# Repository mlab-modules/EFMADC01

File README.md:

# EFMADC01 - Electric Field Mill ADC Module

The **EFMADC01** module is designed to provide an **analog front-end** and **ADC conversion** for [Electric Field Mill sensor](https://github.com/UniversalScientificTechnologies/THUNDERMILL01) development and experiments. It processes analog signals from the field mill electrodes and converts them into digital data for further processing.

## Features

- **High-Precision ADC**: Utilizes the **LTC1865** 16-bit, 250ksps analog-to-digital converter.
- **Low-Noise Analog Front End**: Incorporates **OPA314** operational amplifiers for signal conditioning.
- **Precision and stable Voltage Reference**: Includes a **1.25V reference** for accurate ADC operation.
- **Flexible Power Supply**: Supports **3.3V to 5V** operation.
- **RF Shielding**: Equipped with shielding to reduce external interference.
- **MCX Connector Input**: Enables high-quality signal connection.

## Functional Description

The **EFMADC01** module consists of three main blocks:

1. **Analog Front End (AFE)**:
   - Uses **OPA314** operational amplifiers for signal buffering and amplification.
   - High-impedance resistor (10MΩ) allows direct signal acquisition from the field mill sensor electrodes.

2. **ADC Conversion**:
   - **LTC1865-MS** ADC provides **16-bit resolution** with **250ksps sampling rate**.
   - Accepts differential input signals and supports SPI communication.

3. **Power and Reference**:
   - Powered by an external **3.3V or 5V** supply.
   - Features a **BZV55C-6.2V** Zener diode for overvoltage protection.
   - Uses a **1.25V precision voltage reference** for ADC stability.

## Hardware Connections

### Power Supply:
- **VCC**: Accepts **3.3V to 5V** input.
- **GNDA** and **GND**: Ground connections.

### Analog Input:
- **J9 (MCX Connector)**: Main analog signal input.
- **Operational amplifier stage** conditions the signal before ADC conversion.

## Typical Application

The **EFMADC01** module is primarily used in electric field mill experiments to measure atmospheric electric fields. It can also be employed in low-frequency scientific measurements where high-resolution ADC conversion is required.

## Schematic

For detailed circuit information, please take a look at the [EFMADC01 schematic](/doc/gen/EFMADC01-schematic.pdf) in the documentation.

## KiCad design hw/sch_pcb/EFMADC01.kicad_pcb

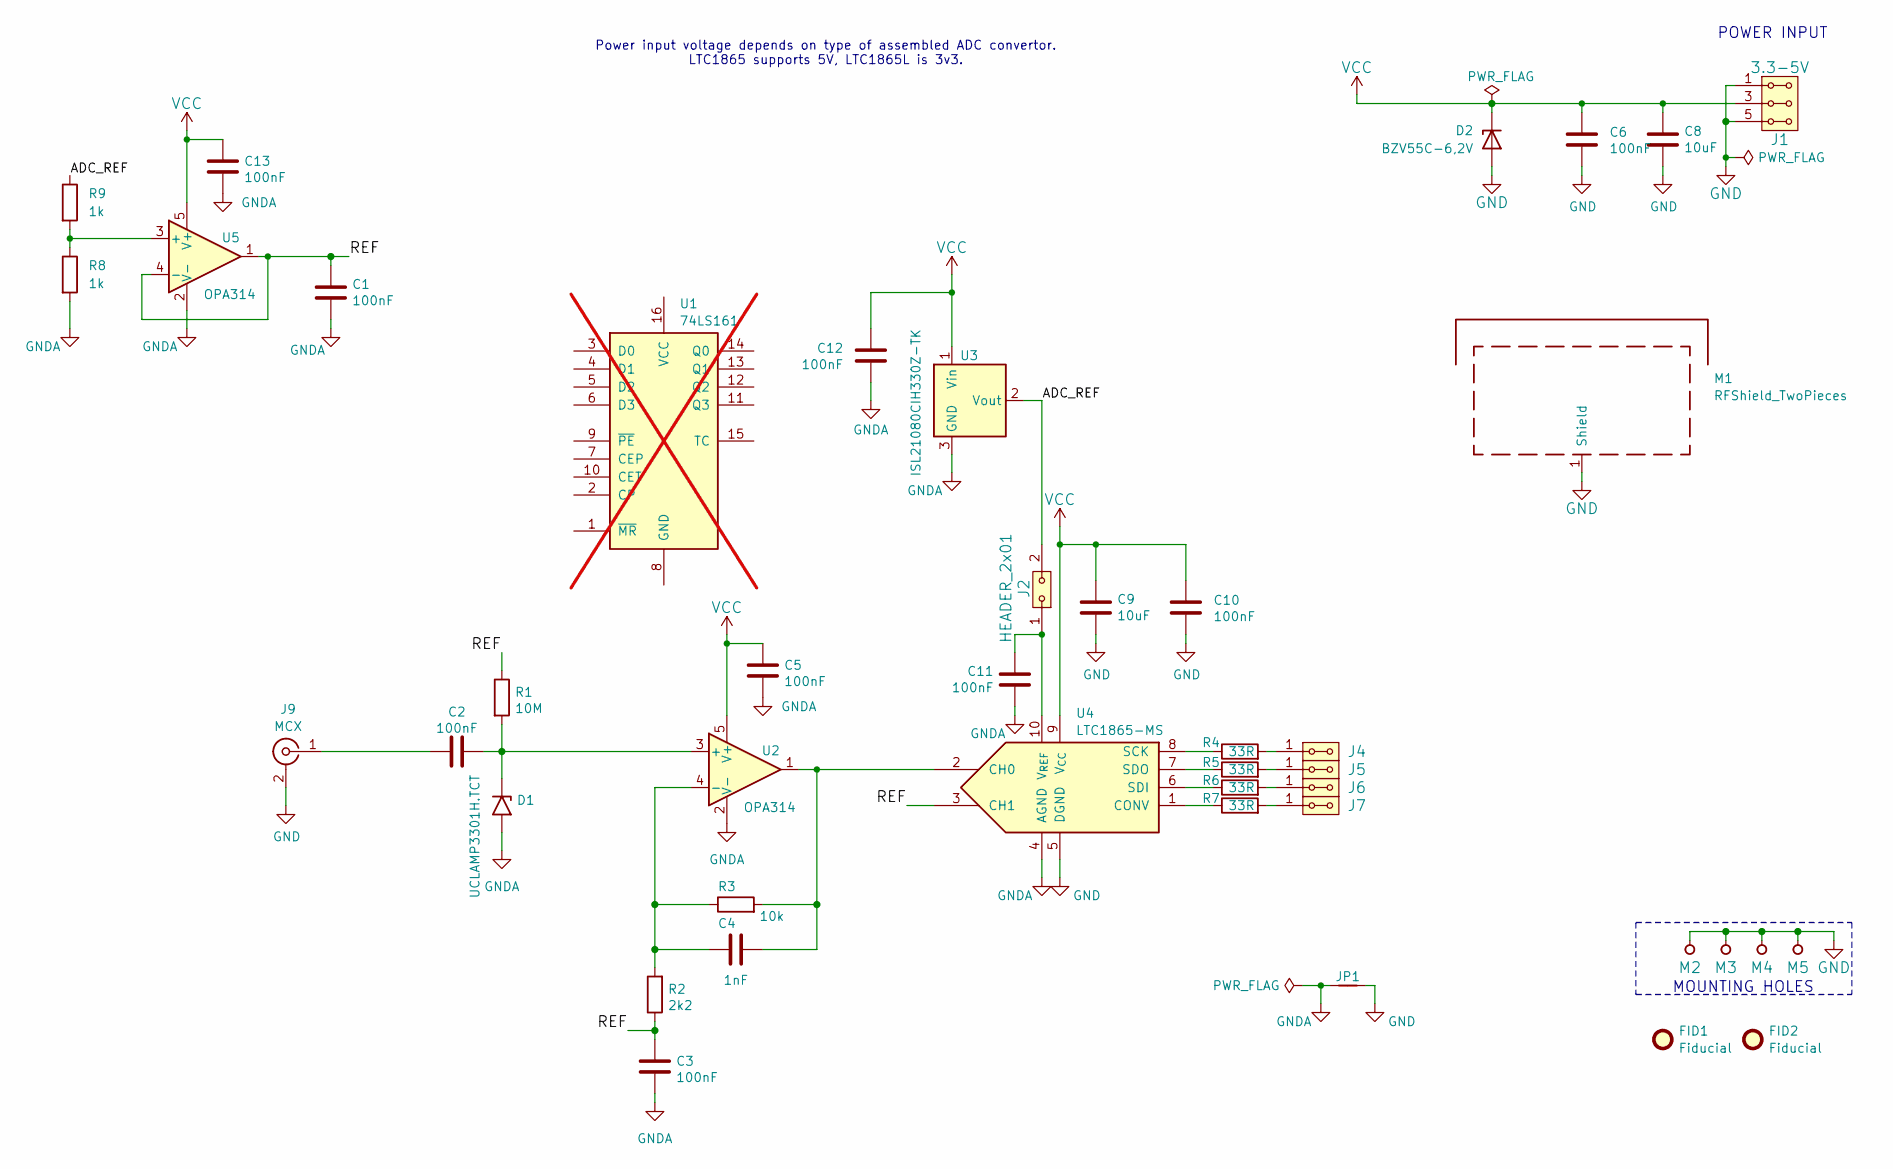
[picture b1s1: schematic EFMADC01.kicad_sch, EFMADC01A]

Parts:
C1, C2, C3, C5, C6, C10, C11, C12, C13: 100nF; C_0805_2012Metric
C4: 1nF; C_0805_2012Metric
C8, C9: 10uF; C_0805_2012Metric
D1: UCLAMP3301H.TCT; D_SMB
D2: BZV55C-6,2V; D_MiniMELF
FID1, FID2: Fiducial; Fiducial_1mm_Mask2mm
J1: 3.3-5V; Straight_2x03
J2: HEADER_2x01; Straight_2x01
J4, J5, J6, J7: HEADER_2x01_PARALLEL; Straight_2x01
J9: MCX; SMA_Amphenol_901-144_Vertical
JP1: Jumper_2_Bridged; NetTie-2_SMD_Pad0.5mm
M1: RFShield_TwoPieces; Laird_Technologies_BMI-S-204-F_32.00x32.00mm
M2, M3, M4, M5: HOLE; MountingHole_3mm
R1: 10M; R_0805_2012Metric
R2: 2k2; R_0805_2012Metric
R3: 10k; R_0805_2012Metric
R4, R5, R6, R7: 33R; R_0805_2012Metric
R8, R9: 1k; R_0805_2012Metric
U1: 74LS161; not fitted
U2, U5: OPA314; SOT-23-5
U3: ISL21080CIH330Z-TK; SOT-23
U4: LTC1865-MS; MSOP-10_3x3mm_P0.5mm

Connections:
/ADC_REF: J2.2, R9.1, U3.2 (Vout)
/REF: C1.1, C3.2, R1.1, R2.1, U4.3 (CH1), U5.1, U5.4 (-)
GND: C6.2, C8.2, C9.2, C10.2, D2.2 (A), J1.1, J1.2, J1.5, J1.6, J9.2 (Ext), JP1.2, M1.1 (Shield), M2.1, M3.1, M4.1, M5.1, U4.5 (DGND)
GNDA: C1.2, C3.1, C5.1, C11.2, C12.2, C13.1, D1.2 (A2), JP1.1, R8.2, U2.2 (V-), U3.3 (GND), U4.4 (AGND), U5.2 (V-)
unnamed: C2.2, D1.1 (A1), R1.2, U2.3 (+)
unnamed: J4.1, J4.2, R4.2
unnamed: J5.1, J5.2, R5.2
unnamed: J6.1, J6.2, R6.2
unnamed: J7.1, J7.2, R7.2
unnamed: C2.1, J9.1 (In)
unnamed: C4.1, R2.2, R3.1, U2.4 (-)
unnamed: C4.2, R3.2, U2.1, U4.2 (CH0)
unnamed: R7.1, U4.1 (CONV)
unnamed: R4.1, U4.8 (SCK)
unnamed: R6.1, U4.6 (SDI)
unnamed: R5.1, U4.7 (SDO)
unnamed: C11.1, J2.1, U4.10 (V_{REF})
unnamed: R8.1, R9.2, U5.3 (+)
VCC: C5.2, C6.1, C8.1, C9.1, C10.1, C12.1, C13.2, D2.1 (K), J1.3, J1.4, U2.5 (V+), U3.1 (Vin), U4.9 (V_{CC}), U5.5 (V+)

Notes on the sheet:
Power input voltage depends on type of assembled ADC convertor. LTC1865 supports 5V, LTC1865L is 3v3.
MOUNTING HOLES
POWER INPUT

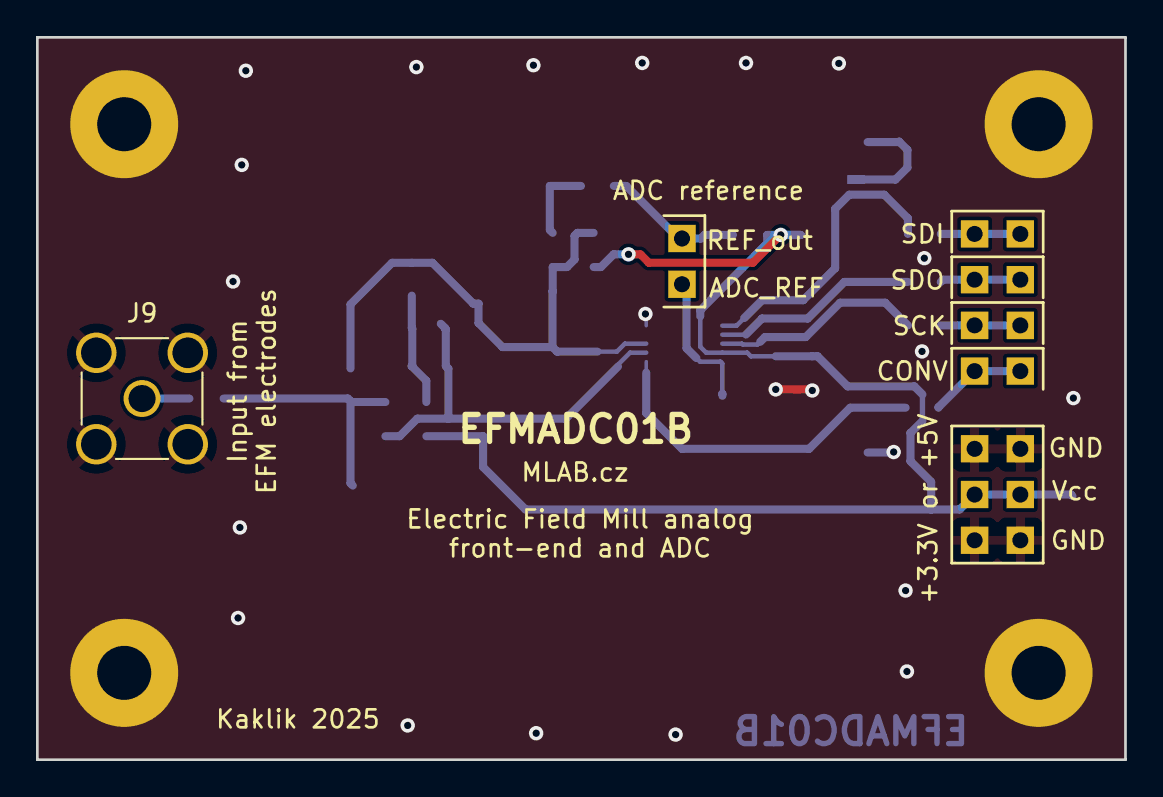
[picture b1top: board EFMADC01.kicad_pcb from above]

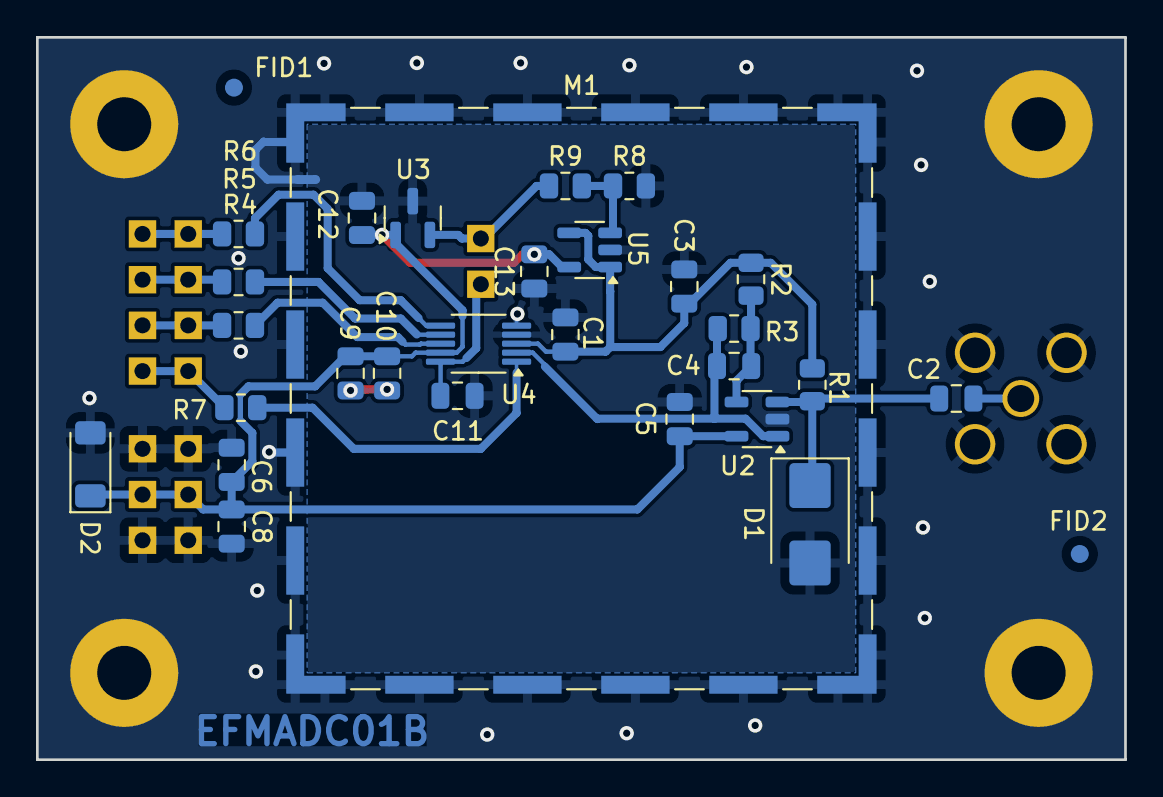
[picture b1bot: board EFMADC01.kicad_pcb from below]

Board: 2 copper layers, 60.5 x 40.1 mm, 42 parts (31 on the bottom side), 19 nets.

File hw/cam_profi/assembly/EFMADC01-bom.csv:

Component,Description,Part,References,Value,Footprint,Quantity Per PCB,Datasheet,ust_id
1,Unpolarized capacitor,C,C4,1nF,C_0805_2012Metric,1,~,5c70984812875079b91f8ba6
2,Unpolarized capacitor,C,C1C2C3C5C6C7C10C11C12,100nF,C_0805_2012Metric,9,~,6508260b462c6d9e720541f1 5c70984712875079b91f8b4c
3,Unpolarized capacitor,C,C8C9,10uF,C_0805_2012Metric,2,~,5c70984812875079b91f8bbe
4,Zener diode,D_Zener,D2,"BZV55C-6,2V",D_MiniMELF,1,~,604b0326128750769e5b0f93
5,"600W unidirectional Transil Transient Voltage Suppressor, 12Vrwm, DO-214AA",SM6T12A,D1,UCLAMP3301H.TCT,D_SMB,1,https://www.st.com/resource/en/datasheet/sm6t.pdf,612514fe1287500165a976f3
6,"2x03 2.54 mm pitch header, 2 pins next to each other are connected",HEADER_2x03_PARALLEL,J1,3.3-5V,Straight_2x03,1,,
7,2x01 2.54 mm pitch header,HEADER_2x01,J2,HEADER_2x01,Straight_2x01,1,,
8,"2x01 2.54 mm pitch header, 2 pins next to each other are connected",HEADER_2x01_PARALLEL,J4J5J6J7,HEADER_2x01_PARALLEL,Straight_2x01,4,,
9,"coaxial connector (BNC, SMA, SMB, SMC, Cinch/RCA, LEMO, ...)",Conn_Coaxial,J9,MCX,SMA_Amphenol_901-144_Vertical,1,~,5fa10cc512875025b39779f6
10,Two-piece EMI RF shielding cabinet,RFShield_TwoPieces,M1,RFShield_TwoPieces,Laird_Technologies_BMI-S-204-F_32.00x32.00mm,1,~,5c72751c1287500b4e11301a
11,Resistor,R,R4R5R6R7,33R,R_0805_2012Metric,4,~,5c70984512875079b91f8970
12,Resistor,R,R2,2k2,R_0805_2012Metric,1,~,5c70984512875079b91f895e
13,Resistor,R,R3,10k,R_0805_2012Metric,1,~,5c70984512875079b91f8962
14,Resistor,R,R1,10M,R_0805_2012Metric,1,~,5c70984712875079b91f8b6d
15,"1.5V 25μA Micropower Voltage Reference, SOT-23",ISL21070CIH320Z-TK,U1,ISL21080CIH315ZT,SOT-23,1,http://www.intersil.com/content/dam/Intersil/documents/fn75/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,5c70984712875079b91f8b0a
16,"2.0V 25μA Micropower Voltage Reference, SOT-23",ISL21070CIH320Z-TK,U3,ISL21080CIH330Z-TK,SOT-23,1,http://www.intersil.com/content/dam/Intersil/documents/fn75/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,67d36d64ee7fc534862c3ebc
17,"Dual channel 16-bit SAR Analog to Digital Converter, 5V supply, 150ksps, SPI interface",LTC1865-MS,U4,LTC1865-MS,MSOP-10_3x3mm_P0.5mm,1,https://www.analog.com/media/en/technical-documentation/data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,651eae84462c6d9e7205573b
18,"50μV V OS, 0.25μV/°C, 35μA CMOS OPERATIONAL AMPLIFIERS, Zerø-Drift Series, SOT",OPA330xxDBV,U2,OPA314,SOT-23-5,1,http://www.ti.com/lit/ds/symlink/opa330.pdf,5c70984412875079b91f879a

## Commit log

2025-02-16 Update metadata files
2025-02-16 Initial schematics of Electric Field milll ADC.
2025-02-16 Update actions products
2025-02-17 Starting layout work.
2025-02-17 Update workflow files
2025-02-19 Rounted PCB Added silkscreen text.
2025-02-20 Update actions scripts manually.
2025-02-20 Improve silkscreen texts.
2025-02-20 Improve layout, adding vias.
2025-02-20 Improve documentation.
2025-02-22 Update metadata.yaml
    Update module status.
2025-02-22 Update README.md
    Improve documentation.
2025-02-22 Update Fab layers.
2025-02-24 Update metadata.yaml
    Fix wrong branches metadata. Select better title image.
2025-04-07 Cleanup net names in schematics.
2025-05-14 Implement buffer to reference voltage.
